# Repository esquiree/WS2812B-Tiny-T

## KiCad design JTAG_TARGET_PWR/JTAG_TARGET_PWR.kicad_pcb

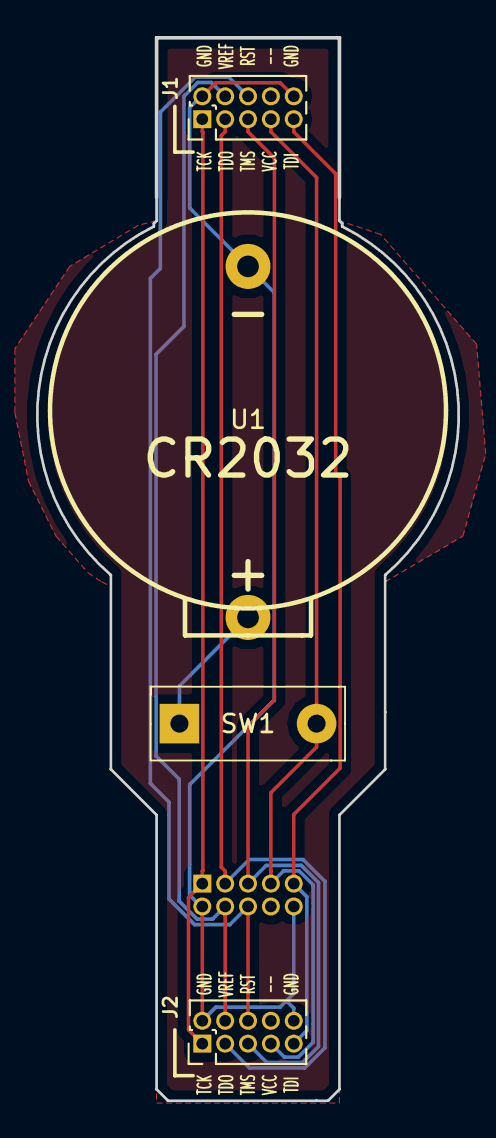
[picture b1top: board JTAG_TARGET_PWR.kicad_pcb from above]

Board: 2 copper layers, 23.4 x 59.1 mm, 5 parts (1 on the bottom side), 9 nets.

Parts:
J1, J2, J3: AVR-JTAG-10; Pin_Header_Straight_2x05_Pitch1.27mm
SW1: SW_SPST; Single Dip Siwtch
U1: Bat; CR2032 Housing

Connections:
GND: J1.2, J1.10, J2.2, J2.10, J3.2, J3.10, U1.1
unnamed: SW1.1, U1.2
RST: J1.6, J2.6, J3.6
TCK: J1.1, J2.1, J3.1
TDI: J1.9, J2.9, J3.9
TDO: J1.3, J2.3, J3.3
TMS: J1.5, J2.5, J3.5
VCC: J1.7, J2.7, J3.7, SW1.2
VREF: J1.4, J2.4, J3.4

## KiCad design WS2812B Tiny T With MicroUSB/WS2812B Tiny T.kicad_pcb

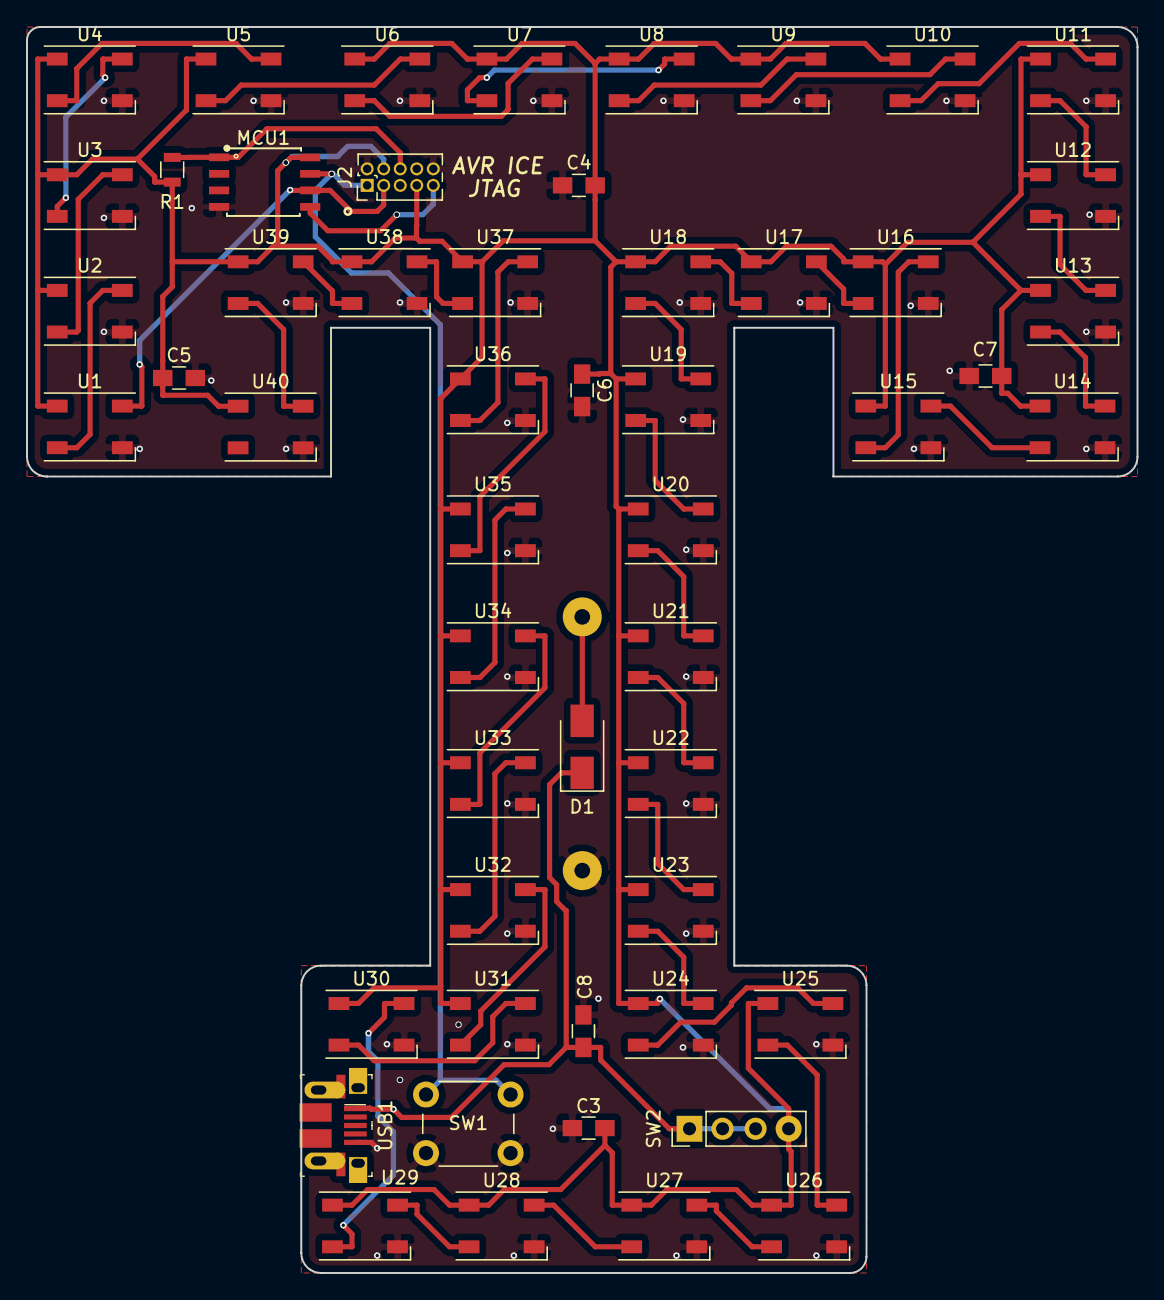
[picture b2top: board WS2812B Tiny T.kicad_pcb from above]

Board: 2 copper layers, 85.3 x 95.8 mm, 54 parts (1 on the bottom side), 47 nets.

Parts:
C3, C4, C5, C6, C7, C8: 0.1uF; C_0805_HandSoldering
D1: D_Schottky; D_SMA
J1: Bat; CR2032 Housing
J2: AVR-JTAG-10; Pin_Header_Straight_2x05_Pitch1.27mm
MCU1: ATtiny85-20SU; ATtiny85_SMD
R1: 10k; R_0805
SW1: SW_Push; SW_PUSH_6mm
SW2: DipSwitch; Pin_Header_Straight_1x04_Pitch2.54mm
U1, U2, U3, U4, U5, U6, U7, U8, U9, U10, U11, U12, U13, U14, U15, U16, U17, U18, U19, U20, U21, U22, U23, U24, U25, U26, U27, U28, U29, U30, U31, U32, U33, U34, U35, U36, U37, U38, U39, U40: WS2812B; LED_WS2812B-PLCC4
USB1: USB_B_Micro; USB_Micro_B_Female_10103594-0001LF

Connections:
+5V: C3.1, C4.1, C5.1, C6.1, C7.1, J2.4, J2.7, MCU1.8, R1.1, SW2.4, U1.1, U2.1, U3.1, U4.1, U5.1, U6.1, U7.1, U8.1, U9.1, U10.1, U11.1, U12.1, U13.1, U14.1, U15.1, U16.1, U17.1, U18.1, U19.1, U20.1, U21.1, U22.1, U23.1, U24.1, U25.1, U26.1, U27.1, U28.1, U29.1, U30.1, U31.1, U32.1, U33.1, U34.1, U35.1, U36.1, U37.1, U38.1, U39.1, U40.1
BTN: J2.1, MCU1.7, SW1.1
DIN: J2.3, MCU1.6, U1.4
GND: C3.2, C4.2, C5.2, C6.2, C7.2, C8.2, J1.1, J2.2, J2.10, MCU1.4, SW1.2, U1.3, U2.3, U3.3, U4.3, U5.3, U6.3, U7.3, U8.3, U9.3, U10.3, U11.3, U12.3, U13.3, U14.3, U15.3, U16.3, U17.3, U18.3, U19.3, U20.3, U21.3, U22.3, U23.3, U24.3, U25.3, U26.3, U27.3, U28.3, U29.3, U30.3, U31.3, U32.3, U33.3, U34.3, U35.3, U36.3, U37.3, U38.3, U39.3, U40.3, USB1.5
unnamed: D1.2, J1.2
unnamed: U1.2, U2.4
unnamed: U2.2, U3.4
unnamed: U3.2, U4.4
unnamed: U4.2, U5.4
unnamed: U5.2, U6.4
unnamed: U6.2, U7.4
unnamed: U7.2, U8.4
unnamed: U8.2, U9.4
unnamed: U10.2, U11.4
unnamed: U9.2, U10.4
unnamed: U11.2, U12.4
unnamed: U12.2, U13.4
unnamed: U13.2, U14.4
unnamed: U14.2, U15.4
unnamed: U15.2, U16.4
unnamed: U16.2, U17.4
unnamed: U17.2, U18.4
unnamed: U18.2, U19.4
unnamed: U19.2, U20.4
unnamed: U20.2, U21.4
unnamed: U21.2, U22.4
unnamed: U22.2, U23.4
unnamed: U23.2, U24.4
unnamed: U24.2, U25.4
unnamed: U25.2, U26.4
unnamed: U26.2, U27.4
unnamed: U27.2, U28.4
unnamed: U28.2, U29.4
unnamed: U29.2, U30.4
unnamed: U30.2, U31.4
unnamed: U31.2, U32.4
unnamed: U32.2, U33.4
unnamed: U33.2, U34.4
unnamed: U34.2, U35.4
unnamed: U35.2, U36.4
unnamed: U36.2, U37.4
unnamed: U37.2, U38.4
unnamed: U38.2, U39.4
unnamed: U39.2, U40.4
PB0: J2.9, MCU1.5
RST: J2.6, MCU1.1, R1.2
VIN_Switch: C8.1, D1.1, SW2.1, SW2.2, SW2.3, USB1.1

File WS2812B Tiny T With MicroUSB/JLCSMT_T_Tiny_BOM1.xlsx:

Comment | References | Footprint
0.1uF | C3 C4 C5 C6 C7 C8 | 0805_C
ATtiny85 | MCU1 | SOIC 8 5.30mm Width
10k | R1 | 0805_R
SMA SCHOTTKEY | D1 | SMA
473460001 | USB1 | usb
WS2812B-B | U1 U2 U3 U4 U5 U6 U7 U8 U9 U10 U11 U12 U13 U14 U15 U16 U17 U18 U19 U20 U21 U22 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 | WS2812B
Jtag | J2 | 1.27mm 10 pos

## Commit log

2019-11-02 Initial Push
